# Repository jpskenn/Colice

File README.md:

# について / About

Colice（コリス）

アリスのレイアウトに発想を得た、部位を組み合わせられるカラムスタッガー（列ずれ）配列の自作キーボード。
Self-made "Col"umnar stagger combinational moduler keyboard, inspired by Al"ice" layout.

## 特徴 / Features

- 一体型かつ分離型でレイアウトが変えられる
- トップマウント形式のケース
- ロータリーエンコーダを2個使用可能
- 総当たりマトリクス（2乗マトリクス）を採用
Pro Micro 1個で全てを制御
- I2C用のピンは未使用
- LEDチョットダケ光る
- 本来のケース外形はもっと丸い感じでかわいい
発注時ミスで、v.0.2は四角い外形になっている

## キー配列 / Layout

## 写真

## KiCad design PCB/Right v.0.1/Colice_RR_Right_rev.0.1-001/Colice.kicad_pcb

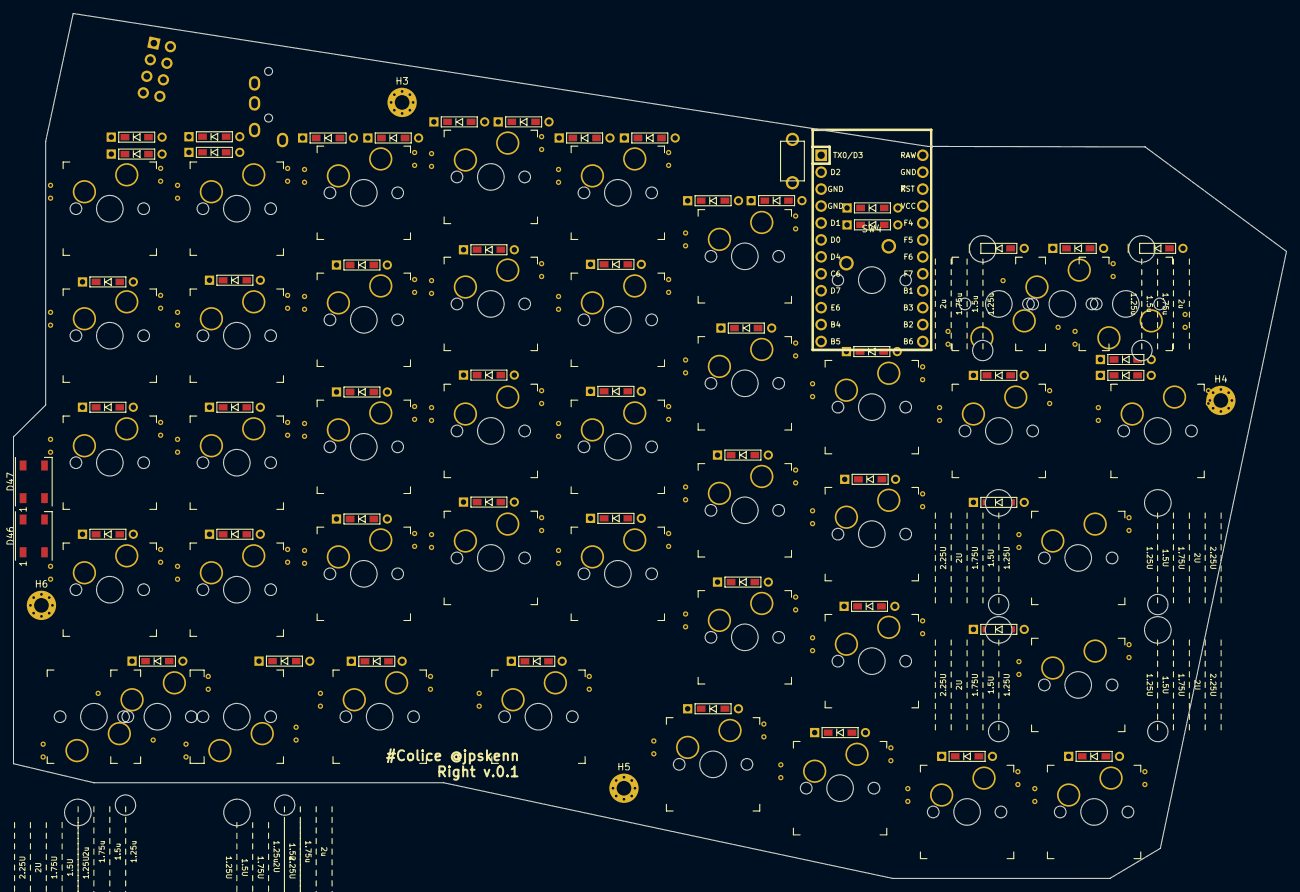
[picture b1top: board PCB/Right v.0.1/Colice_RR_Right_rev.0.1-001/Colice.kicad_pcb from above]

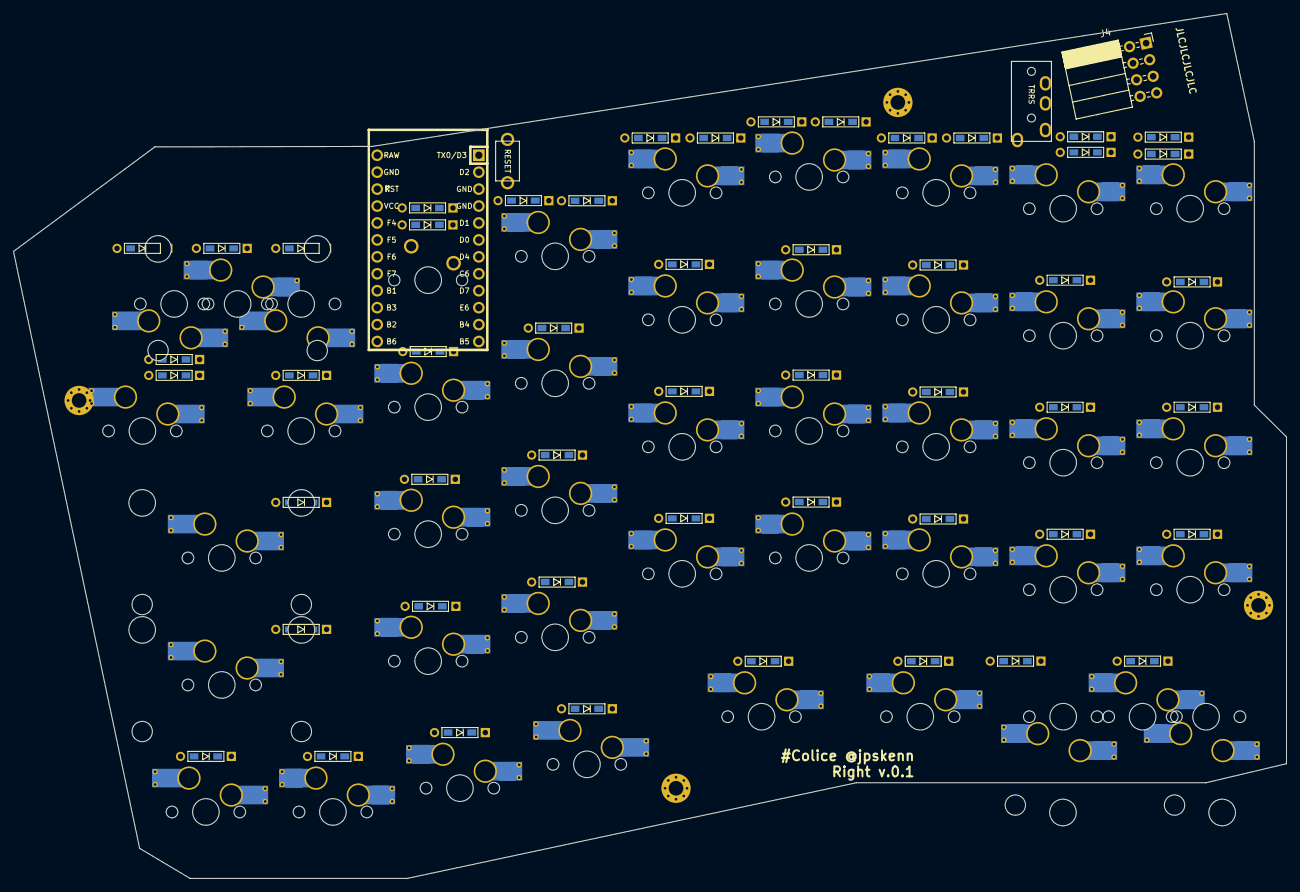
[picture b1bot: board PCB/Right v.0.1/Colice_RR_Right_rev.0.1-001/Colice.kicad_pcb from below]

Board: 2 copper layers, 190.9 x 129.7 mm, 109 parts (4 on the bottom side), 66 nets, no tracks yet.

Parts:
D1, D2, D3, D4, D5, D6, D7, D8, D9, D10, D11, D12, D13, D14, D15, D16, D17, D18, D19, D20, D21, D22, D23, D24, D25, D26, D27, D28, D29, D30, D31, D32, D33, D34, D35, D36, D37, D38, D39, D40, D41, D42, D43, D44, D45, D48, D49, D50, D51, D52, D53: D; D3_TH_SMD
D46, D47: WS2812B; LED_WS2812B_PLCC4_5.0x5.0mm_P3.2mm
H1, H7, H8: MountingHole; CherryMX_MidHeight_Choc_Hotswap_2.25U_Outline
H2: MountingHole; CherryMX_MidHeight_Choc_Hotswap_2U_Outline
H3, H4, H5, H6: MountingHole; MountingHole_2.2mm_M2_Pad_Via
J3: MJ-4PP-9
J4: Conn_02x04_Counter_Clockwise; PinSocket_2x04_P2.54mm_Horizontal
SW1: SW_Push; ResetSW
SW2, SW3, SW5, SW6, SW7, SW8, SW9, SW10, SW11, SW12, SW13, SW14, SW15, SW16, SW17, SW18, SW19, SW20, SW21, SW22, SW23, SW24, SW25, SW26, SW27, SW28, SW29, SW30, SW31, SW32, SW33, SW34, SW35, SW36, SW37, SW38, SW39, SW40, SW41, SW42, SW43, SW44, SW45: SW_Push; CherryMX_Hotswap_v2
SW4: SW_Push; SW_Cherry_MX1A_1.00u_PCB
U1: ProMicro; ArduinoProMicro

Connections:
GND1: D46.3, D47.3, J3.C, SW1.2, U1.3, U1.4, U1.23
unnamed: D1.1, SW2.1, SW3.1, SW41.1, SW42.1, SW43.1, SW44.1
unnamed: D2.2, SW2.2, SW41.2
unnamed: D3.2, SW3.2
unnamed: D4.1, SW4.1, SW5.1, SW6.1, SW7.1, SW8.1
unnamed: D5.2, SW4.2
unnamed: D6.2, SW5.2
unnamed: D7.2, SW6.2
unnamed: D8.2, SW7.2
unnamed: D9.2, SW8.2
unnamed: D10.1, SW9.1, SW10.1, SW11.1, SW12.1, SW45.1
unnamed: D11.2, SW9.2
unnamed: D12.2, SW10.2
unnamed: D13.2, SW11.2
unnamed: D14.2, SW12.2
unnamed: D15.1, SW13.1, SW39.1, SW40.1
unnamed: D16.1, SW14.1, SW15.1, SW16.1, SW17.1, SW18.1
unnamed: D17.2, SW14.2
unnamed: D18.2, SW15.2
unnamed: D19.2, SW16.2
unnamed: D20.2, SW17.2
unnamed: D21.2, SW18.2
unnamed: D22.1, SW19.1, SW20.1, SW21.1, SW22.1, SW23.1
unnamed: D23.2, SW19.2
unnamed: D24.2, SW20.2
unnamed: D25.2, SW21.2
unnamed: D26.2, SW22.2
unnamed: D27.2, SW23.2
unnamed: D28.1, SW24.1, SW25.1, SW26.1, SW27.1, SW28.1
unnamed: D29.2, SW24.2
unnamed: D30.2, SW25.2
unnamed: D31.2, SW26.2
unnamed: D32.2, SW27.2
unnamed: D33.2, SW28.2
unnamed: D34.1, SW29.1, SW30.1, SW31.1, SW32.1, SW33.1, SW38.1
unnamed: D35.2, SW29.2
unnamed: D36.2, SW30.2
unnamed: D37.2, SW31.2
unnamed: D38.2, SW32.2
unnamed: D39.2, SW13.2
unnamed: D41.2, SW34.2
unnamed: D42.2, SW35.2
unnamed: D43.2, SW36.2
unnamed: D44.2, SW37.2
unnamed: D45.2, SW33.2, SW38.2
unnamed: D46.2, D47.4
unnamed: D48.2, SW39.2
unnamed: D49.2, SW40.2
unnamed: D50.2, SW42.2
unnamed: D51.2, SW43.2
unnamed: D52.2, SW44.2
unnamed: D53.2, SW45.2
VCC: D46.1, D47.1, J3.D, U1.21
data: J3.B, U1.2
led: D46.4, U1.1
pin1: D2.1, D5.1, D11.1, D16.2, D39.1, U1.17
pin2: D6.1, D12.1, D22.2, D48.1, D50.1, U1.16
pin3: D7.1, D13.1, D28.2, D51.1, U1.15
pin4: D8.1, D14.1, D34.2, D52.1, U1.14
pin5: D3.1, D9.1, D40.2, D49.1, D53.1, U1.13
pin6: D17.1, D23.1, D29.1, D35.1, D41.1, J4.1, U1.8
pin7: D15.2, D18.1, D24.1, D30.1, D36.1, D42.1, J4.2, U1.9
pin8: D1.2, D19.1, D25.1, D31.1, D37.1, D43.1, J4.3, U1.10
pin9: D4.2, D20.1, D26.1, D32.1, D38.1, D44.1, J4.4, U1.11
pin10: D10.2, D21.1, D27.1, D33.1, D40.1, D45.1, J4.5, SW34.1, SW35.1, SW36.1, SW37.1, U1.12
reset: SW1.1, U1.22

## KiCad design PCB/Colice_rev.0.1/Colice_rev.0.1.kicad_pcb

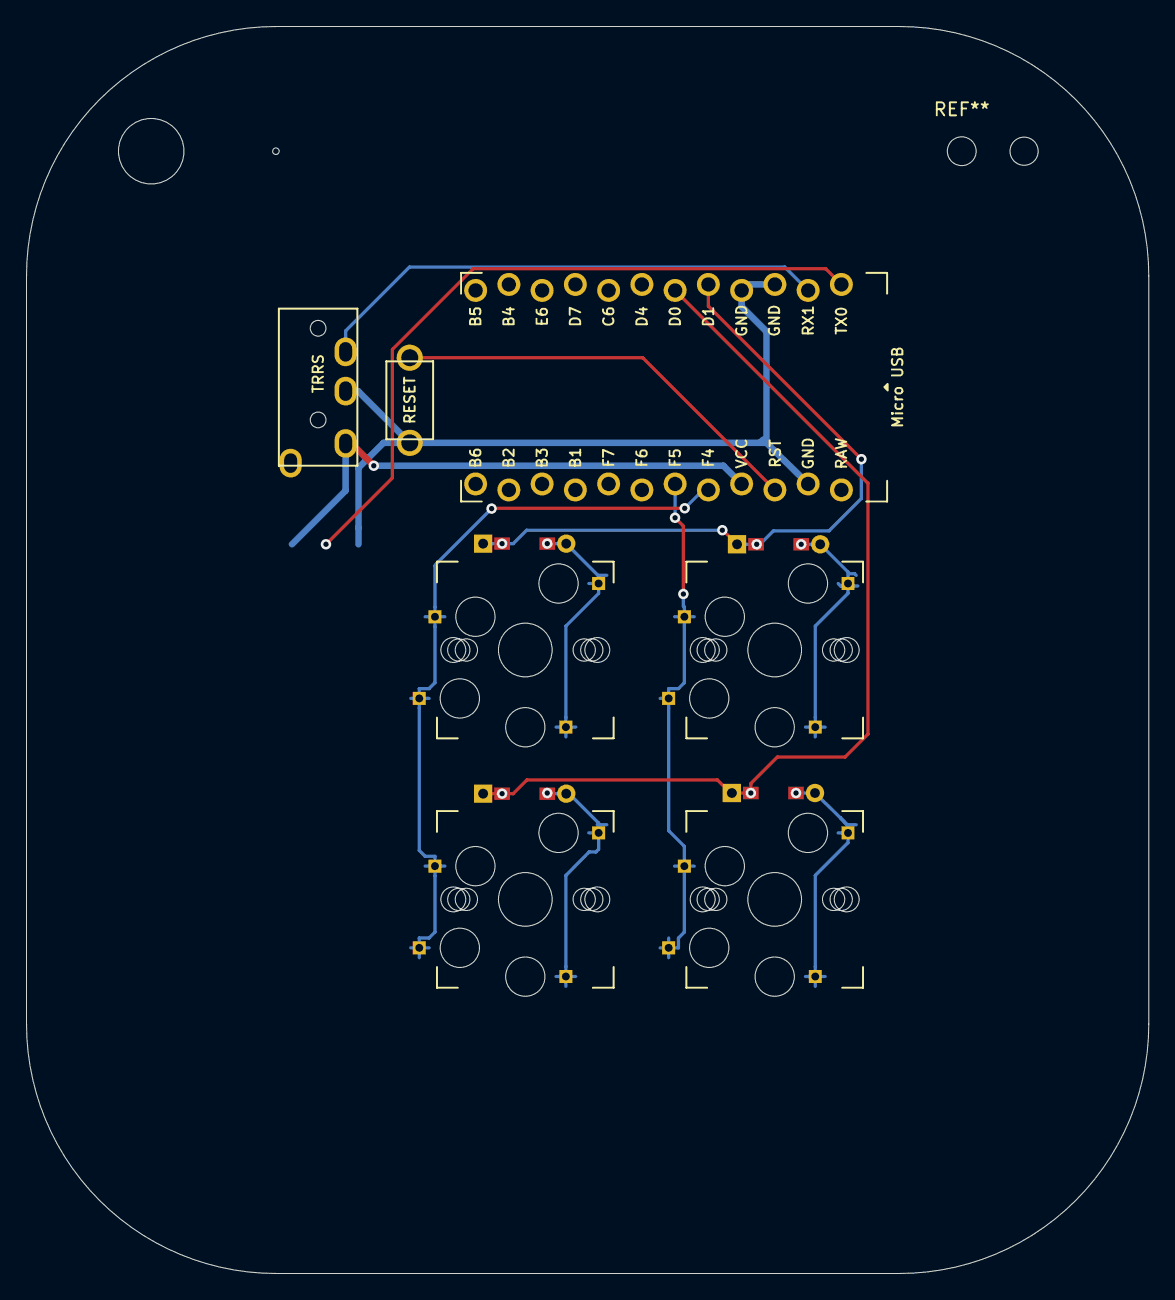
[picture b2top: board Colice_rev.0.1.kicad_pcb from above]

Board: 2 copper layers, 85.7 x 95.2 mm, 13 parts (0 on the bottom side), 13 nets.

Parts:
D1, D2, D3, D4: D; diode_TH_SMD_rev2
J1: MJ-4PP-9
J2: LED; StripLED_rev2
Ref**: Val**; IM_HOLE
SW1: SW_Push; ResetSW
SW2, SW3, SW4, SW5: SW_Push; CherryMX_MidHeight_Choc_Hotswap_rev5
U1: pro_micro; ArduinoProMicro-ZigZag_rev5

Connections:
GND: J1.C, J2.1, SW1.2, U1.3, U1.4, U1.23
unnamed: D1.2, SW2.2
unnamed: D2.2, SW3.2
unnamed: D3.2, SW4.2
unnamed: D4.2, SW5.2
VCC: J1.D, J2.3, U1.21
col0: SW2.1, SW3.1, U1.20
col1: SW4.1, SW5.1, U1.19
data: J1.B, U1.2
led: J2.2, U1.1
reset: SW1.1, U1.22
row0: D1.1, D3.1, U1.5
row1: D2.1, D4.1, U1.6

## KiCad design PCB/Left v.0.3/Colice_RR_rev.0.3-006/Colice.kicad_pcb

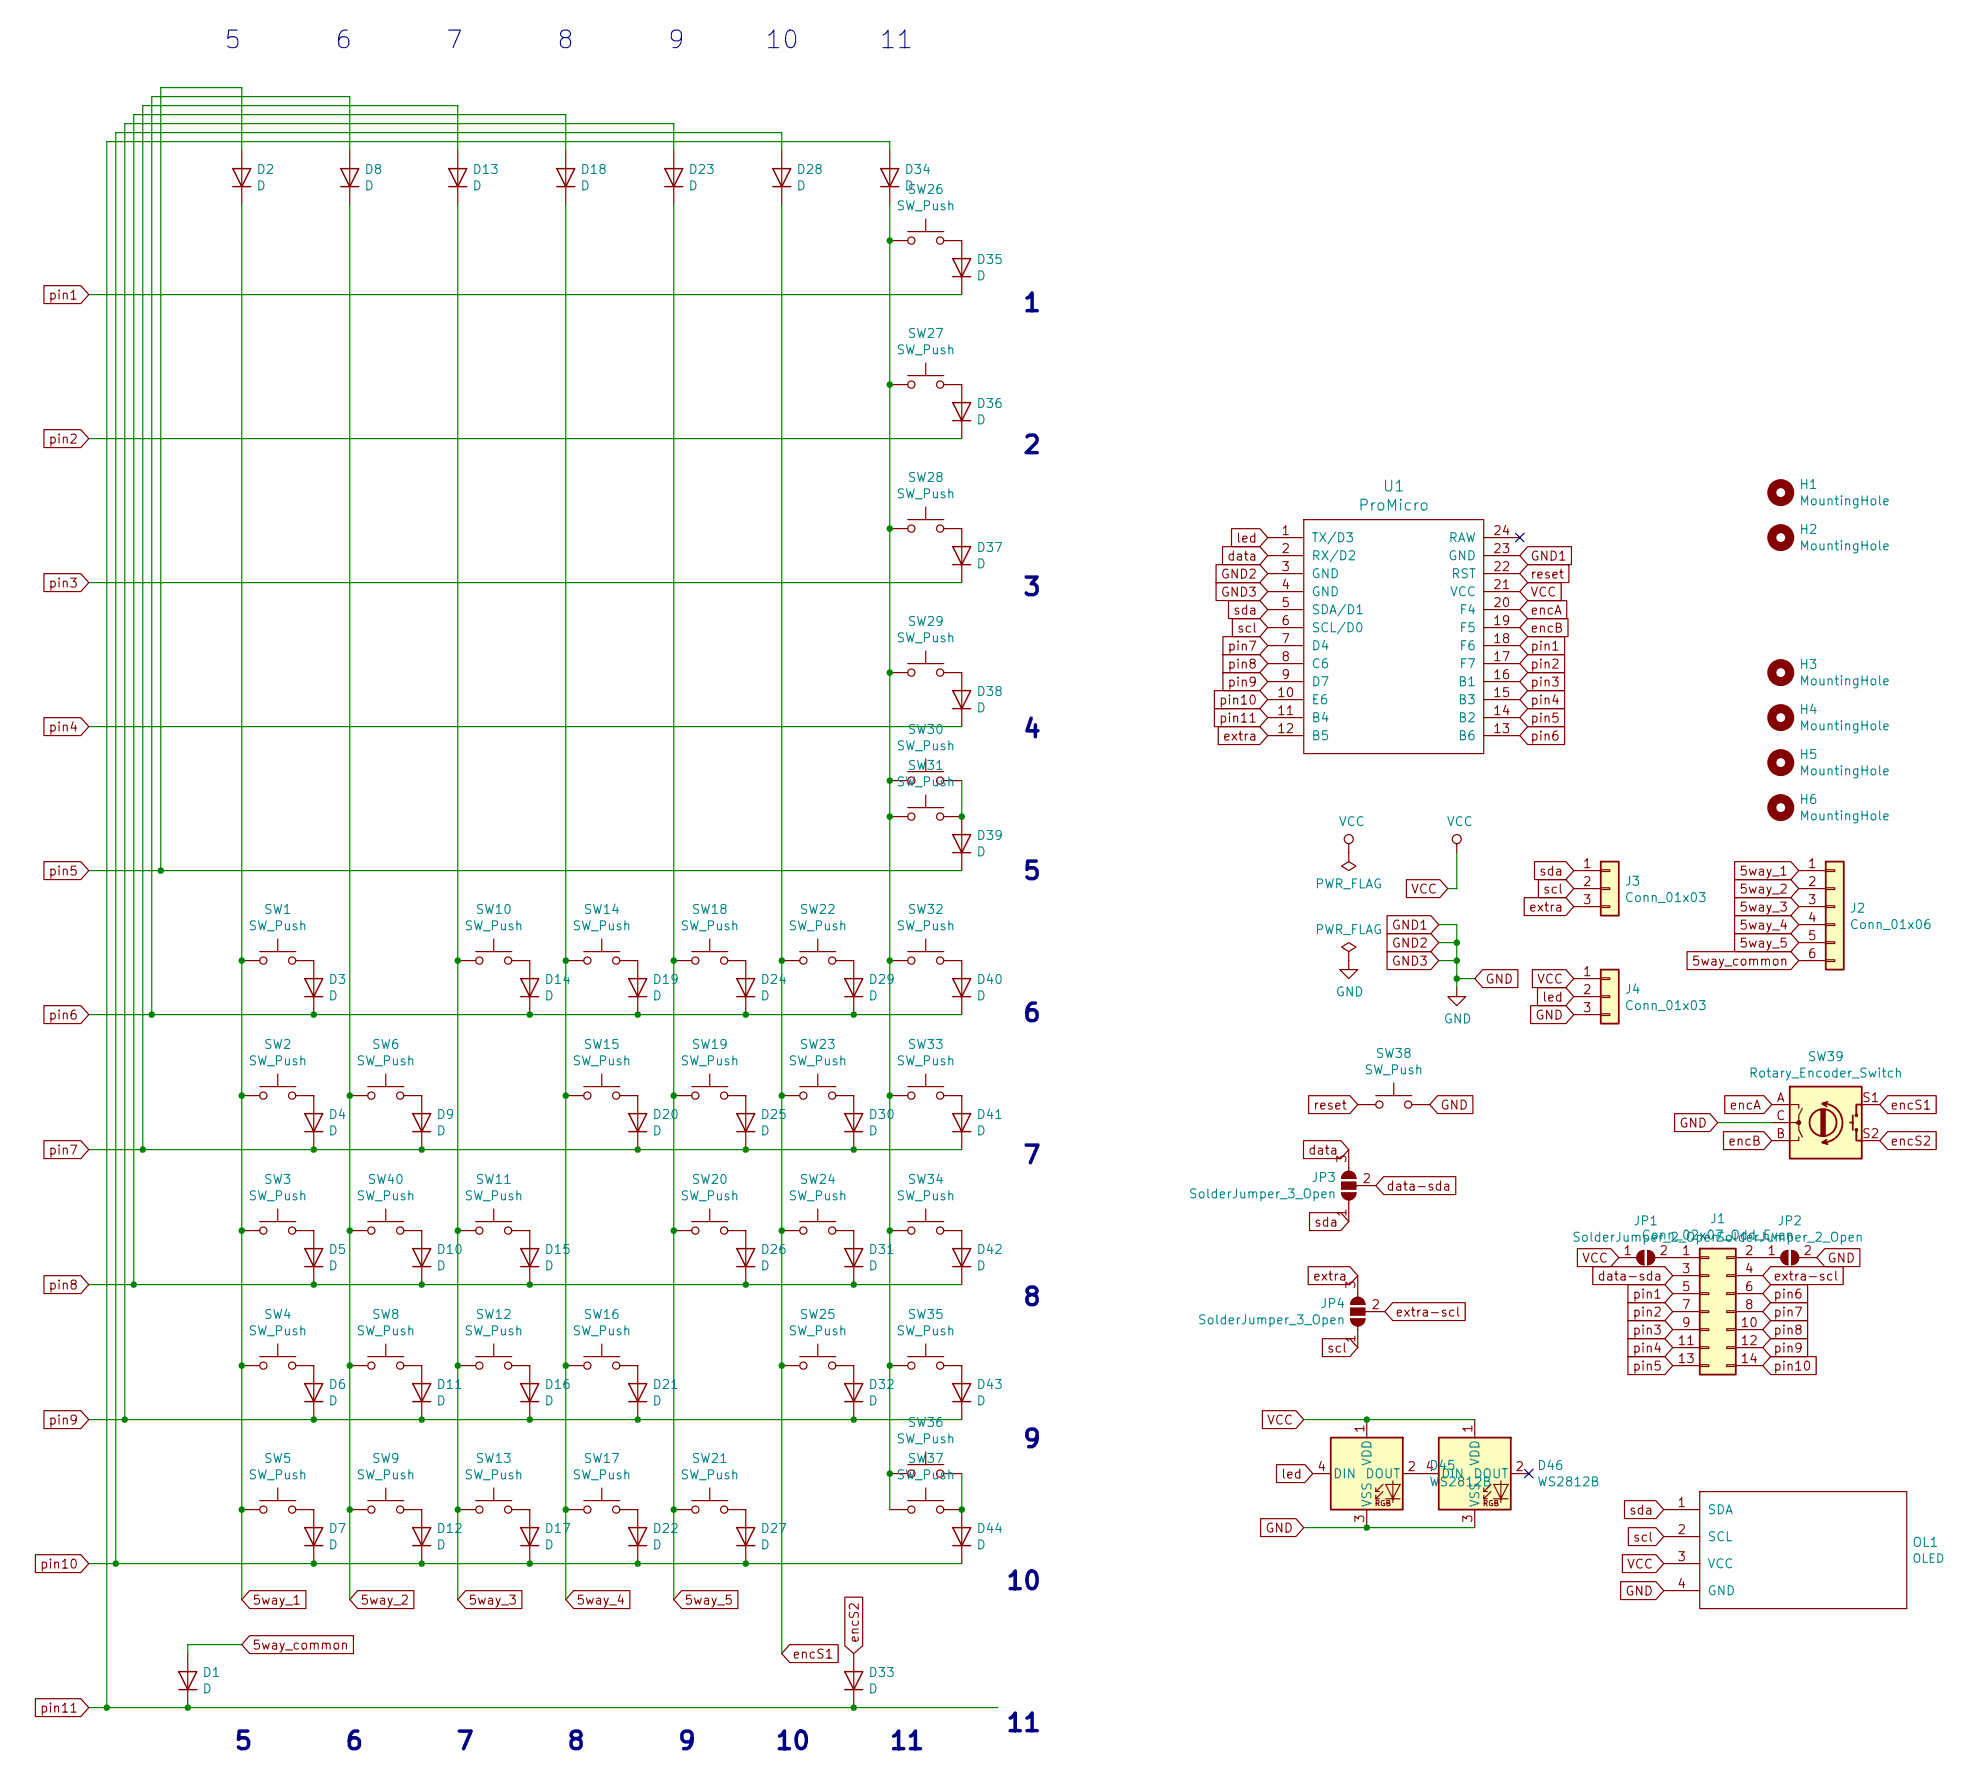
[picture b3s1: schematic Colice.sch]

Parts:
D1, D2, D3, D4, D5, D6, D7, D8, D9, D10, D11, D12, D13, D14, D15, D16, D17, D18, D19, D20, D21, D22, D23, D24, D25, D26, D27, D28, D29, D30, D31, D32, D33, D34, D35, D36, D37, D38, D39, D40, D41, D42, D43, D44: D; D3_TH_SMD
D45, D46: WS2812B; LED_WS2812B_PLCC4_5.0x5.0mm_P3.2mm
H1: MountingHole; CherryMX_MidHeight_Choc_Hotswap_2U_Outline
H2: MountingHole; CherryMX_MidHeight_Choc_Hotswap_2.75U_Outline
H3, H4, H5, H6: MountingHole; MountingHole_2.2mm_M2_Pad_Via
J1: Conn_02x07_Odd_Even; PinHeader_2x07_P2.54mm_Horizontal
J2: Conn_01x06; PinHeader_1x06_P2.54mm_Vertical
J3, J4: Conn_01x03; PinHeader_1x03_P2.54mm_Vertical
JP1, JP2: SolderJumper_2_Open; SolderJumper-2_P1.3mm_Open_Pad1.0x1.5mm
JP3, JP4: SolderJumper_3_Open; SolderJumper-3_P1.3mm_Open_Pad1.0x1.5mm
OL1: OLED; OLED_1side
SW1, SW2, SW3, SW4, SW5, SW8, SW9, SW10, SW11, SW12, SW13, SW14, SW15, SW16, SW17, SW18, SW19, SW20, SW21, SW22, SW23, SW24, SW25, SW26, SW27, SW28, SW29, SW30, SW31, SW32, SW33, SW34, SW35, SW36, SW37: SW_Push; CherryMX_Hotswap_v2
SW6, SW40: SW_Push; SW_Cherry_MX1A_1.00u_PCB
SW38: SW_Push; SW_Tactile_SPST_Angled_MJTP1117
SW39: Rotary_Encoder_Switch; RotaryEncoder_Alps_EC11E-Switch_Vertical_H20mm_rev2
U1: ProMicro; ProMicro_v3

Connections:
5way_1: D2.1 (K), J2.1, SW1.1, SW2.1, SW3.1, SW4.1, SW5.1
5way_2: D8.1 (K), J2.2, SW6.1, SW8.1, SW9.1, SW40.1
5way_3: D13.1 (K), J2.3, SW10.1, SW11.1, SW12.1, SW13.1
5way_4: D18.1 (K), J2.4, SW14.1, SW15.1, SW16.1, SW17.1
5way_5: D23.1 (K), J2.5, SW18.1, SW19.1, SW20.1, SW21.1
5way_common: D1.2 (A), J2.6
GND: D45.3 (VSS), D46.3 (VSS), J4.3, JP2.2 (B), OL1.4 (GND), SW38.2, SW39.C, U1.3 (GND), U1.4 (GND), U1.23 (GND); also elsewhere on the board
unnamed: D3.2 (A), SW1.2
unnamed: D4.2 (A), SW2.2
unnamed: D5.2 (A), SW3.2
unnamed: D6.2 (A), SW4.2
unnamed: D7.2 (A), SW5.2
unnamed: D9.2 (A), SW6.2
unnamed: D10.2 (A), SW40.2
unnamed: D11.2 (A), SW8.2
unnamed: D12.2 (A), SW9.2
unnamed: D14.2 (A), SW10.2
unnamed: D15.2 (A), SW11.2
unnamed: D16.2 (A), SW12.2
unnamed: D17.2 (A), SW13.2
unnamed: D19.2 (A), SW14.2
unnamed: D20.2 (A), SW15.2
unnamed: D21.2 (A), SW16.2
unnamed: D22.2 (A), SW17.2
unnamed: D24.2 (A), SW18.2
unnamed: D25.2 (A), SW19.2
unnamed: D26.2 (A), SW20.2
unnamed: D27.2 (A), SW21.2
unnamed: D29.2 (A), SW22.2
unnamed: D30.2 (A), SW23.2
unnamed: D31.2 (A), SW24.2
unnamed: D32.2 (A), SW25.2
unnamed: D34.1 (K), SW26.1, SW27.1, SW28.1, SW29.1, SW30.1, SW31.1, SW32.1, SW33.1, SW34.1, SW35.1, SW36.1, SW37.1
unnamed: D35.2 (A), SW26.2
unnamed: D36.2 (A), SW27.2
unnamed: D37.2 (A), SW28.2
unnamed: D38.2 (A), SW29.2
unnamed: D39.2 (A), SW30.2, SW31.2
unnamed: D40.2 (A), SW32.2
unnamed: D41.2 (A), SW33.2
unnamed: D42.2 (A), SW34.2
unnamed: D43.2 (A), SW35.2
unnamed: D44.2 (A), SW36.2, SW37.2
unnamed: D45.2 (DOUT), D46.4 (DIN)
unnamed 45: J1.1, JP1.2 (B); also elsewhere on the board
unnamed 46: J1.2, JP2.1 (A); also elsewhere on the board
VCC: D45.1 (VDD), D46.1 (VDD), J4.1, JP1.1 (A), OL1.3 (VCC), U1.21 (VCC); also elsewhere on the board
data: JP3.3 (B), U1.2 (RX/D2); also elsewhere on the board
data-sda: J1.3, JP3.2 (C); also elsewhere on the board
encA: SW39.A, U1.20 (F4)
encB: SW39.B, U1.19 (F5)
encS1: D28.1 (K), SW22.1, SW23.1, SW24.1, SW25.1, SW39.S1
encS2: D33.2 (A), SW39.S2
extra: J3.3, JP4.3 (B), U1.12 (B5); also elsewhere on the board
extra-scl: J1.4, JP4.2 (C); also elsewhere on the board
led: D45.4 (DIN), J4.2, U1.1 (TX/D3)
pin1: D35.1 (K), J1.5, U1.18 (F6)
pin2: D36.1 (K), J1.7, U1.17 (F7)
pin3: D37.1 (K), J1.9, U1.16 (B1)
pin4: D38.1 (K), J1.11, U1.15 (B3)
pin5: D2.2 (A), D39.1 (K), J1.13, U1.14 (B2)
pin6: D3.1 (K), D8.2 (A), D14.1 (K), D19.1 (K), D24.1 (K), D29.1 (K), D40.1 (K), J1.6, U1.13 (B6)
pin7: D4.1 (K), D9.1 (K), D13.2 (A), D20.1 (K), D25.1 (K), D30.1 (K), D41.1 (K), J1.8, U1.7 (D4)
pin8: D5.1 (K), D10.1 (K), D15.1 (K), D18.2 (A), D26.1 (K), D31.1 (K), D42.1 (K), J1.10, U1.8 (C6)
pin9: D6.1 (K), D11.1 (K), D16.1 (K), D21.1 (K), D23.2 (A), D32.1 (K), D43.1 (K), J1.12, U1.9 (D7)
pin10: D7.1 (K), D12.1 (K), D17.1 (K), D22.1 (K), D27.1 (K), D28.2 (A), D44.1 (K), J1.14, U1.10 (E6)
pin11: D1.1 (K), D33.1 (K), D34.2 (A), U1.11 (B4)
reset: SW38.1, U1.22 (RST)
scl: J3.2, JP4.1 (A), OL1.2 (SCL), U1.6 (SCL/D0); also elsewhere on the board
sda: J3.1, JP3.1 (A), OL1.1 (SDA), U1.5 (SDA/D1); also elsewhere on the board

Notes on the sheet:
5 6 7 8 9 10 11
1 2 3 4 5 6 7 8 9 10 11

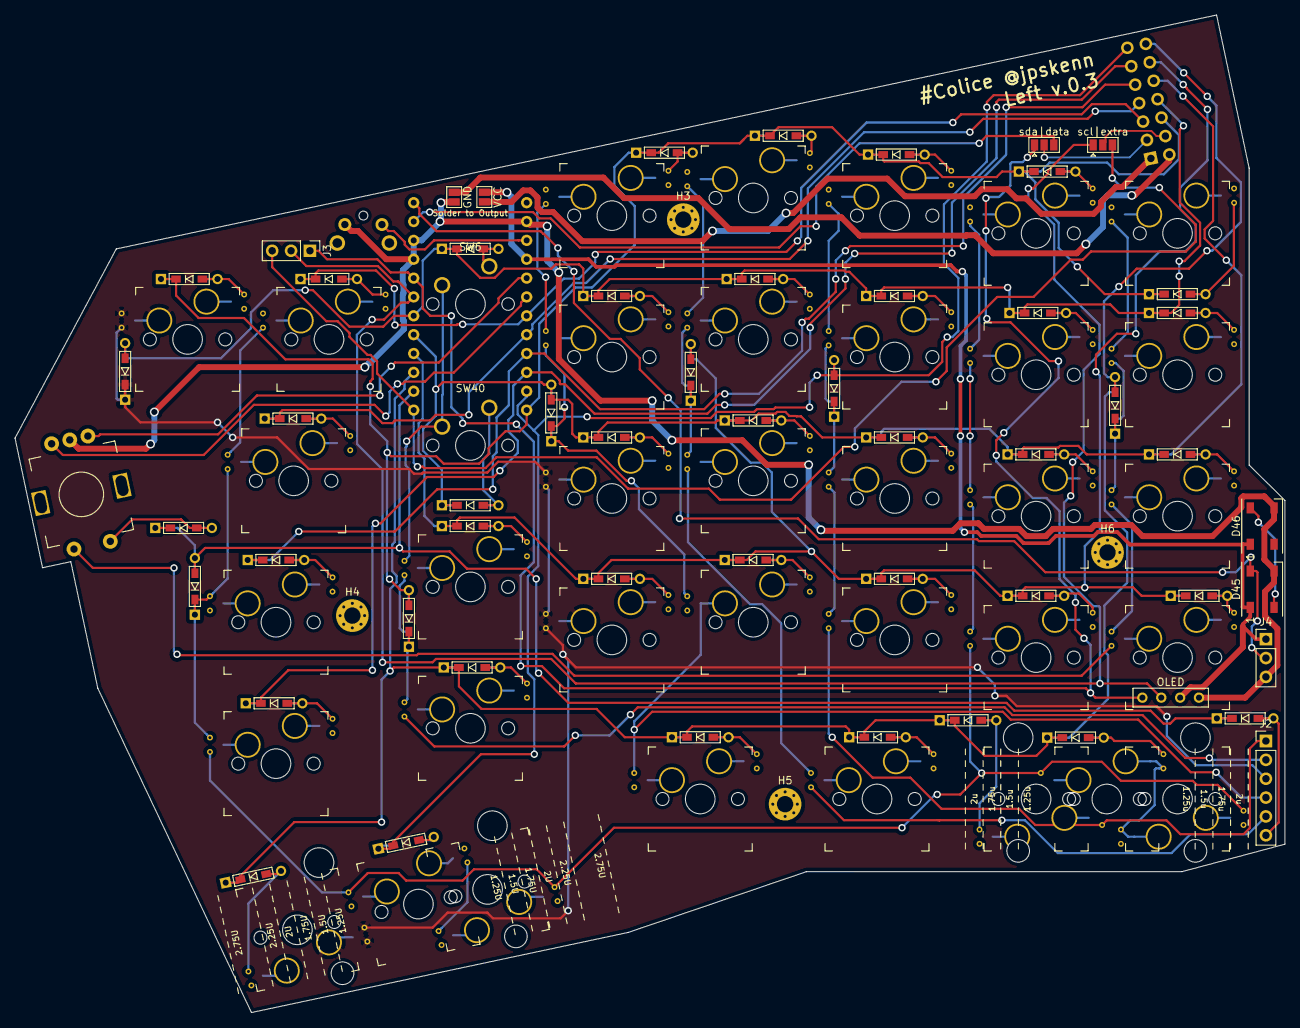
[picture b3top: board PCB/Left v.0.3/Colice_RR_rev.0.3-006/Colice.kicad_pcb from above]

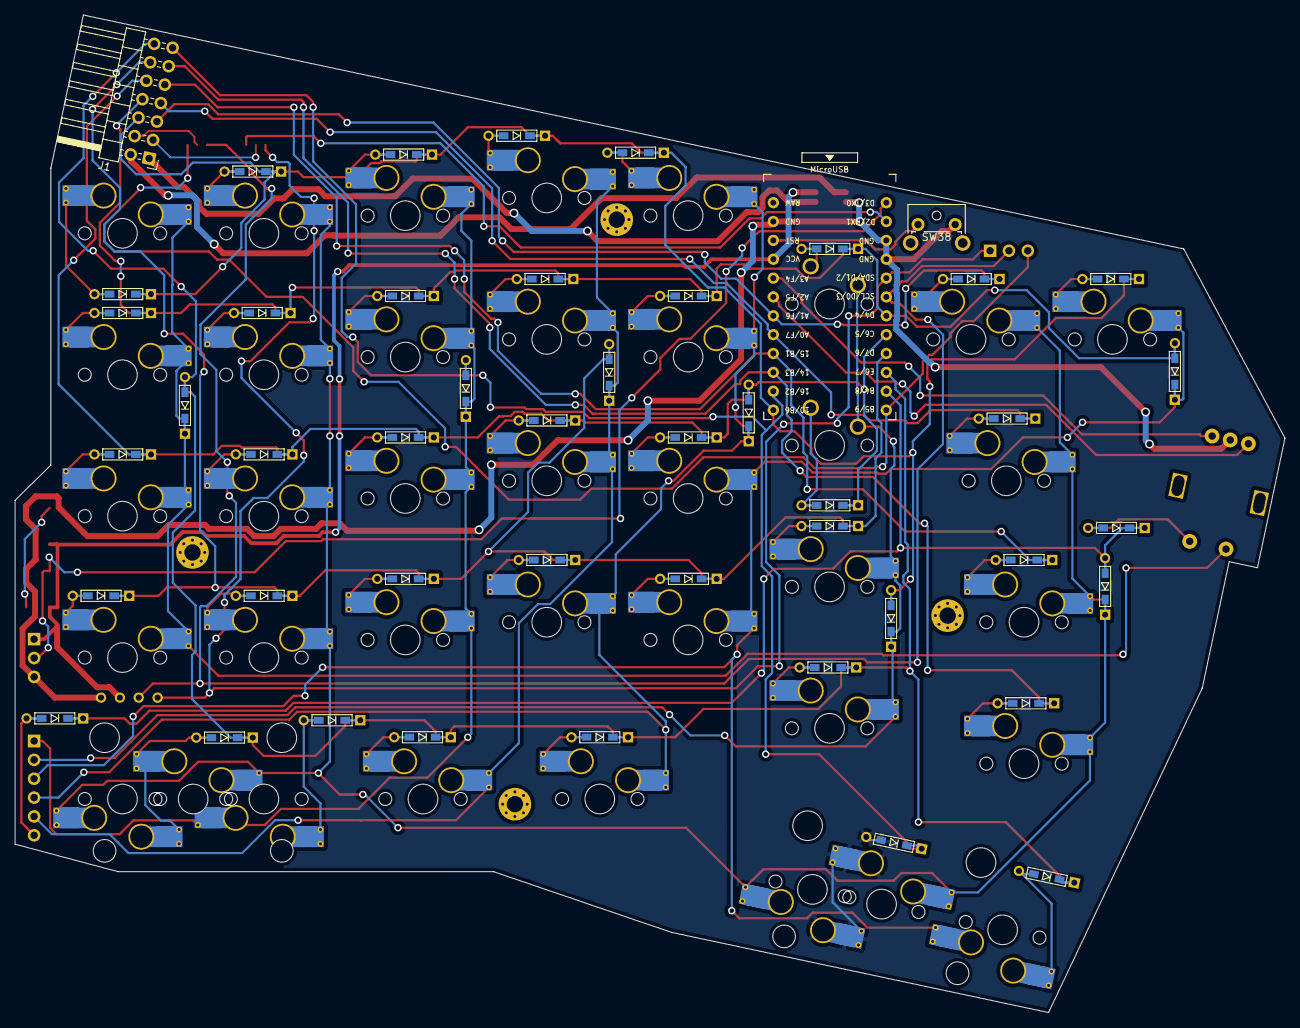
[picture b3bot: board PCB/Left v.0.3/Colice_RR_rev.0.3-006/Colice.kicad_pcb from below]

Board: 2 copper layers, 171.1 x 134.4 mm, 101 parts (3 on the bottom side), 70 nets.

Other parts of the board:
  scl|extra: SolderJumper_3_Open; SolderJumper-3_P1.3mm_Open_Pad1.0x1.5mm
 sda|data: SolderJumper_3_Open; SolderJumper-3_P1.3mm_Open_Pad1.0x1.5mm
GND: SolderJumper_2_Open; SolderJumper-2_P1.3mm_Open_Pad1.0x1.5mm
VCC: SolderJumper_2_Open; SolderJumper-2_P1.3mm_Open_Pad1.0x1.5mm

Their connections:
GND: GND.2; also elsewhere on the board
unnamed 45: VCC.2; also elsewhere on the board
unnamed 46: GND.1; also elsewhere on the board
VCC: VCC.1; also elsewhere on the board
data: sda|data.3; also elsewhere on the board
data-sda: sda|data.2; also elsewhere on the board
extra: scl|extra.3; also elsewhere on the board
extra-scl: scl|extra.2; also elsewhere on the board
scl: scl|extra.1; also elsewhere on the board
sda: sda|data.1; also elsewhere on the board

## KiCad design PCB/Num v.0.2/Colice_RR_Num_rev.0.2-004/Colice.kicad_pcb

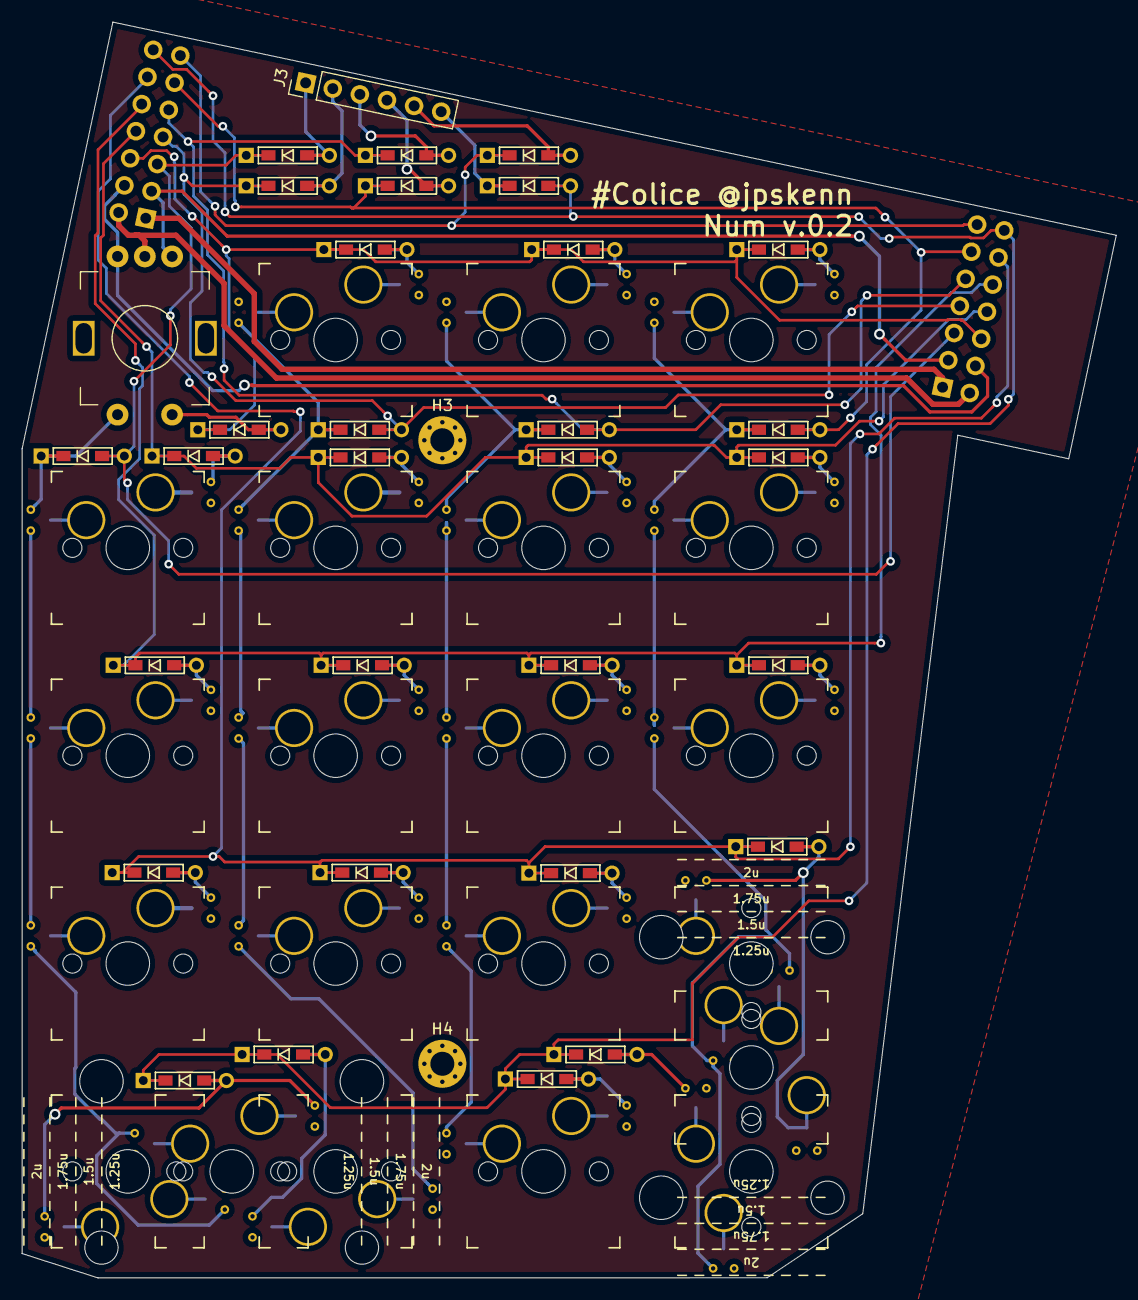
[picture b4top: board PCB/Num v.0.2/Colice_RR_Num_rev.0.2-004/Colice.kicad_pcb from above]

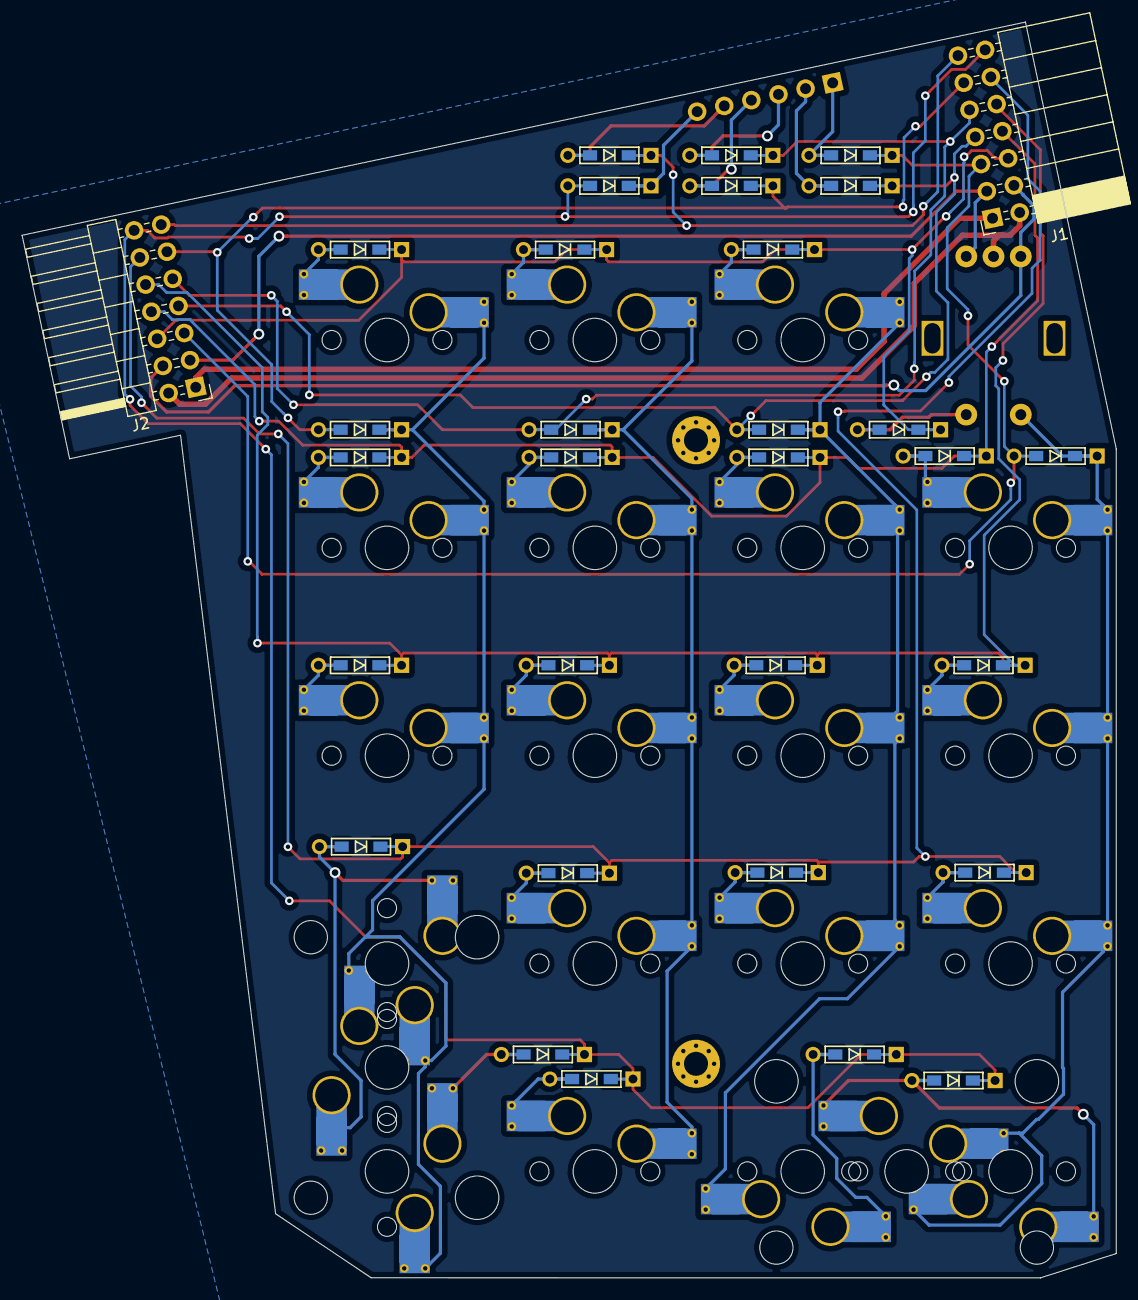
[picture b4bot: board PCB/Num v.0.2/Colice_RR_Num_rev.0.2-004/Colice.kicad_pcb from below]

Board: 2 copper layers, 100.3 x 115.1 mm, 59 parts (2 on the bottom side), 44 nets.

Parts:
D1, D2, D3, D4, D5, D6, D7, D8, D9, D10, D11, D12, D13, D14, D15, D16, D17, D18, D19, D20, D21, D22, D23, D24, D25, D26, D27, D28, D29, D30: D; D3_TH_SMD
H1, H2: MountingHole; CherryMX_MidHeight_Choc_Hotswap_2U_Outline
H3, H4: MountingHole; MountingHole_2.2mm_M2_Pad_Via
J1: Conn_02x07_Odd_Even; PinSocket_2x07_P2.54mm_Horizontal
J2: Conn_02x07_Odd_Even; PinHeader_2x07_P2.54mm_Horizontal
J3: Conn_01x06; PinHeader_1x06_P2.54mm_Vertical
SW1, SW2, SW3, SW4, SW5, SW6, SW7, SW8, SW9, SW10, SW11, SW12, SW13, SW14, SW15, SW16, SW17, SW18, SW19, SW20, SW21: SW_Push; CherryMX_Hotswap_v2
SW22: Rotary_Encoder_Switch; RotaryEncoder_Alps_EC11E-Switch_Vertical_H20mm_rev2

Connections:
5way_1: D26.2, J3.1
5way_2: D27.2, J3.2
5way_3: D28.2, J3.3
5way_4: D29.2, J3.4
5way_5: D30.2, J3.5
5way_common: D25.1, J3.6
GND_source: J1.2, J2.2, SW22.C
unnamed: D2.2, SW1.2
unnamed: D3.2, SW2.2
unnamed: D4.2, SW3.2
unnamed: D5.2, SW4.2, SW20.2
unnamed: D6.1, SW5.1, SW6.1, SW7.1, SW8.1, SW18.1
unnamed: D7.2, SW5.2
unnamed: D8.2, SW6.2
unnamed: D9.2, SW7.2
unnamed: D10.2, SW8.2
unnamed: D11.1, SW9.1, SW10.1, SW11.1, SW12.1, SW13.1
unnamed: D12.2, SW9.2
unnamed: D13.2, SW10.2
unnamed: D14.2, SW11.2
unnamed: D15.2, SW12.2
unnamed: D16.2, SW13.2
unnamed: D17.1, SW14.1, SW15.1, SW16.1, SW17.1, SW19.1, SW21.1
unnamed: D18.2, SW14.2
unnamed: D19.2, SW15.2
unnamed: D20.2, SW16.2
unnamed: D21.2, SW17.2, SW21.2
unnamed: D22.2, SW18.2
unnamed: D23.2, SW19.2
VCC_source: J1.1, J2.1
encS1: D1.1, SW1.1, SW2.1, SW3.1, SW4.1, SW20.1, SW22.S1
encS2: D24.2, SW22.S2
pin1: D1.2, D26.1, J1.5, J2.5
pin2: D6.2, D27.1, J1.7, J2.7
pin3: D11.2, D28.1, J1.9, J2.9
pin4: D17.2, D29.1, J1.11, J2.11
pin5: D30.1, J1.13, J2.13
pin6: D7.1, D12.1, D18.1, D24.1, J1.6, J2.6
pin7: D2.1, D8.1, D13.1, D19.1, J1.8, J2.8
pin8: D3.1, D9.1, D14.1, D20.1, J1.10, J2.10
pin9: D4.1, D10.1, D15.1, D21.1, J1.12, J2.12
pin10: D5.1, D16.1, D22.1, D23.1, D25.2, J1.14, J2.14
scl-extra: J1.4, J2.4, SW22.B
sda-data: J1.3, J2.3, SW22.A
